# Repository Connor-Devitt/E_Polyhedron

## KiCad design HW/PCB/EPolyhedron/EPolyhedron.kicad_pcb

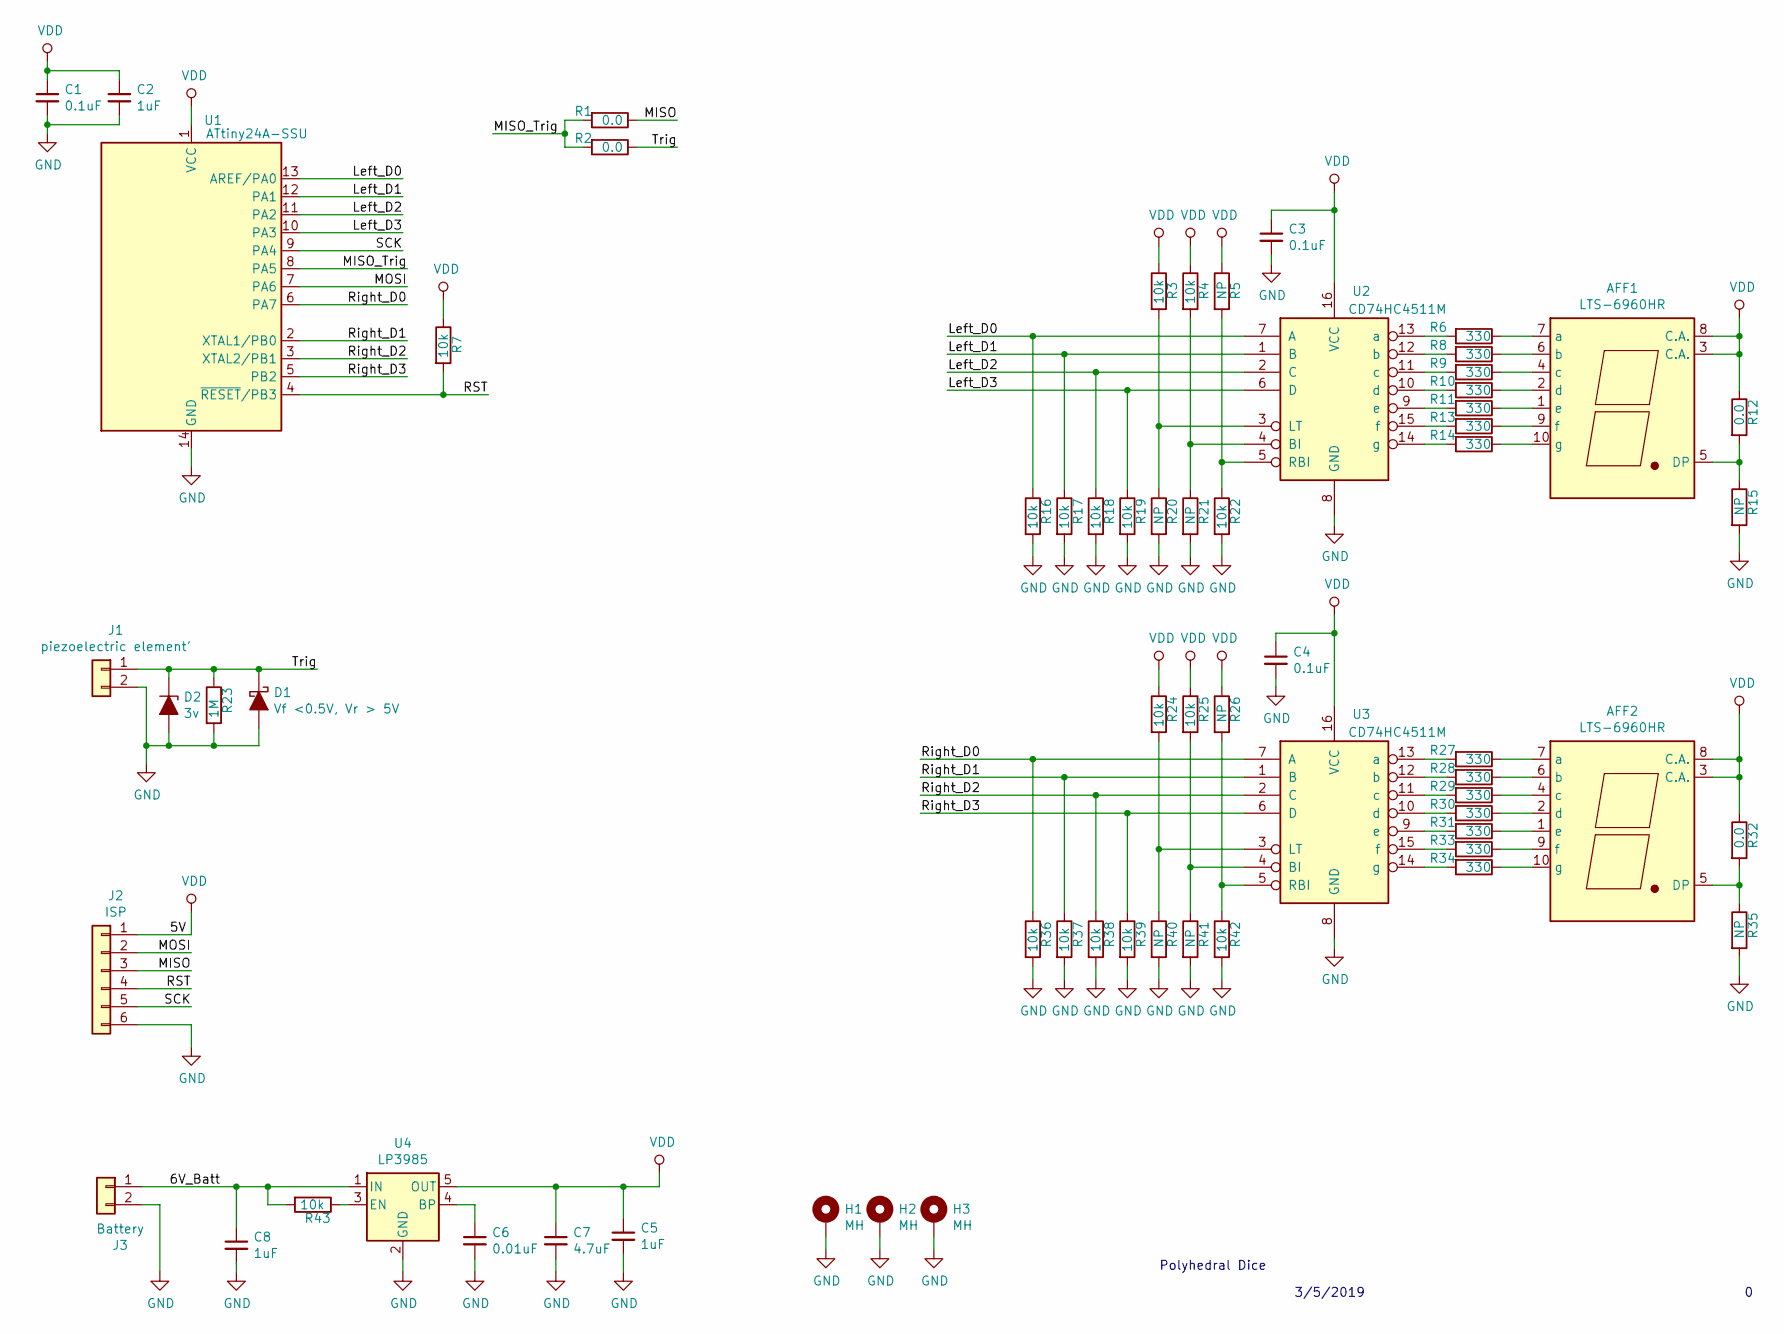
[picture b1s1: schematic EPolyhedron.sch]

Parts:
AFF1, AFF2: LTS-6960HR; 7SegmentLED_LTS6760_LTS6780
C1, C3, C4: 0.1uF; C_0402_1005Metric
C2, C5, C8: 1uF; C_0402_1005Metric
C6: 0.01uF; C_0402_1005Metric
C7: 4.7uF; C_0402_1005Metric
D1: Vf <0.5V, Vr > 5V; D_SOD-323_HandSoldering
D2: 3v; D_SOD-323_HandSoldering
H1, H2, H3: MH; MountingHole_2.2mm_M2_Pad
J1: piezoelectric element'; PinHeader_1x02_P1.27mm_Vertical
J2: ISP; PinHeader_1x06_P1.27mm_Vertical
J3: Battery; BatteryHolder_Keystone_106_1x20mm
R1, R2, R12, R32: 0.0; R_0402_1005Metric
R3, R4, R7, R16, R17, R18, R19, R22, R24, R25, R36, R37, R38, R39, R42, R43: 10k; R_0402_1005Metric
R5, R15, R20, R21, R26, R35, R40, R41: NP; R_0402_1005Metric
R6, R8, R9, R10, R11, R13, R14, R27, R28, R29, R30, R31, R33, R34: 330; R_0402_1005Metric
R23: 1M; R_0402_1005Metric
U1: ATtiny24A-SSU; SOIC-14_3.9x8.7mm_P1.27mm
U2, U3: CD74HC4511M; SOIC-16_3.9x9.9mm_P1.27mm
U4: LP3985; SOT-23-5_HandSoldering

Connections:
/6V_Batt: C8.1, J3.1, R43.2, U4.1 (IN)
/Left_D0: R16.1, U1.13 (AREF/PA0), U2.7 (A)
/Left_D1: R17.1, U1.12 (PA1), U2.1 (B)
/Left_D2: R18.1, U1.11 (PA2), U2.2 (C)
/Left_D3: R19.1, U1.10 (PA3), U2.6 (D)
/MISO: J2.3, R1.1
/MISO_Trig: R1.2, R2.2, U1.8 (PA5)
/MOSI: J2.2, U1.7 (PA6)
/RST: J2.4, R7.2, U1.4 (~RESET~/PB3)
/Right_D0: R36.1, U1.6 (PA7), U3.7 (A)
/Right_D1: R37.1, U1.2 (XTAL1/PB0), U3.1 (B)
/Right_D2: R38.1, U1.3 (XTAL2/PB1), U3.2 (C)
/Right_D3: R39.1, U1.5 (PB2), U3.6 (D)
/SCK: J2.5, U1.9 (PA4)
/Trig: D1.1 (K), D2.1 (K), J1.1, R2.1, R23.1
GND: C1.2, C2.2, C3.2, C4.2, C5.2, C6.2, C7.2, C8.2, D1.2 (A), D2.2 (A), H1.1, H2.1, H3.1, J1.2, J2.6, J3.2, R15.2, R16.2, R17.2, R18.2, R19.2, R20.2, R21.2, R22.2, R23.2, R35.2, R36.2, R37.2, R38.2, R39.2, R40.2, R41.2, R42.2, U1.14 (GND), U2.8 (GND), U3.8 (GND), U4.2 (GND)
unnamed: AFF1.1 (e), R11.1
unnamed: AFF1.2 (d), R10.1
unnamed: AFF1.4 (c), R9.1
unnamed: AFF1.5 (DP), R12.2, R15.1
unnamed: AFF1.6 (b), R8.1
unnamed: AFF1.7 (a), R6.1
unnamed: AFF1.9 (f), R13.1
unnamed: AFF1.10 (g), R14.1
unnamed: AFF2.1 (e), R31.1
unnamed: AFF2.2 (d), R30.1
unnamed: AFF2.4 (c), R29.1
unnamed: AFF2.5 (DP), R32.2, R35.1
unnamed: AFF2.6 (b), R28.1
unnamed: AFF2.7 (a), R27.1
unnamed: AFF2.9 (f), R33.1
unnamed: AFF2.10 (g), R34.1
unnamed: C6.1, U4.4 (BP)
unnamed: R6.2, U2.13 (a)
unnamed: R8.2, U2.12 (b)
unnamed: R9.2, U2.11 (c)
unnamed: R10.2, U2.10 (d)
unnamed: R11.2, U2.9 (e)
unnamed: R13.2, U2.15 (f)
unnamed: R14.2, U2.14 (g)
unnamed: R3.2, R20.1, U2.3 (LT)
unnamed: R4.2, R21.1, U2.4 (BI)
unnamed: R5.2, R22.1, U2.5 (RBI)
unnamed: R24.2, R40.1, U3.3 (LT)
unnamed: R25.2, R41.1, U3.4 (BI)
unnamed: R26.2, R42.1, U3.5 (RBI)
unnamed: R27.2, U3.13 (a)
unnamed: R28.2, U3.12 (b)
unnamed: R29.2, U3.11 (c)
unnamed: R30.2, U3.10 (d)
unnamed: R31.2, U3.9 (e)
unnamed: R33.2, U3.15 (f)
unnamed: R34.2, U3.14 (g)
unnamed: R43.1, U4.3 (EN)
VDD: AFF1.3 (C.A.), AFF1.8 (C.A.), AFF2.3 (C.A.), AFF2.8 (C.A.), C1.1, C2.1, C3.1, C4.1, C5.1, C7.1, J2.1, R3.1, R4.1, R5.1, R7.1, R12.1, R24.1, R25.1, R26.1, R32.1, U1.1 (VCC), U2.16 (VCC), U3.16 (VCC), U4.5 (OUT)

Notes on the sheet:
3/5/2019
Polyhedral Dice

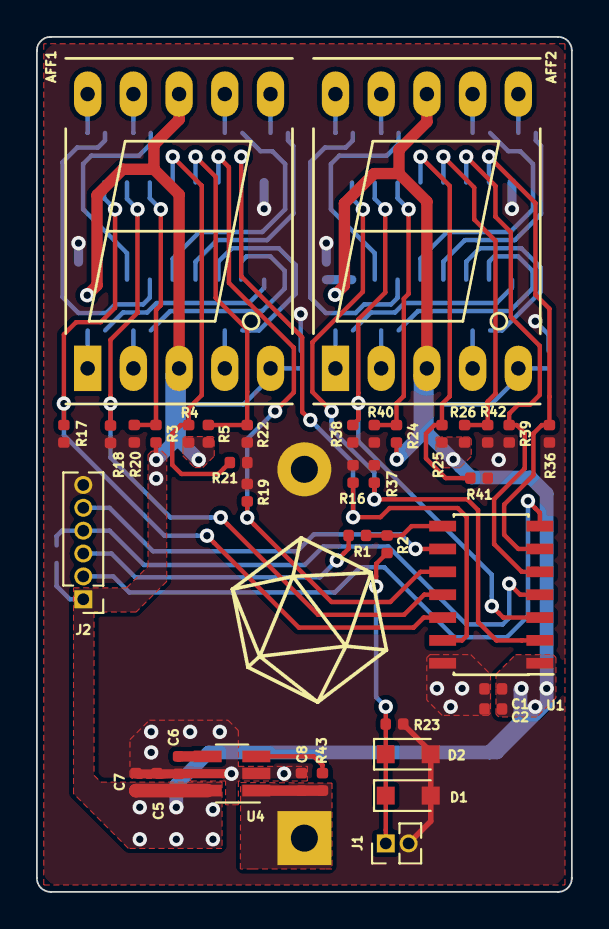
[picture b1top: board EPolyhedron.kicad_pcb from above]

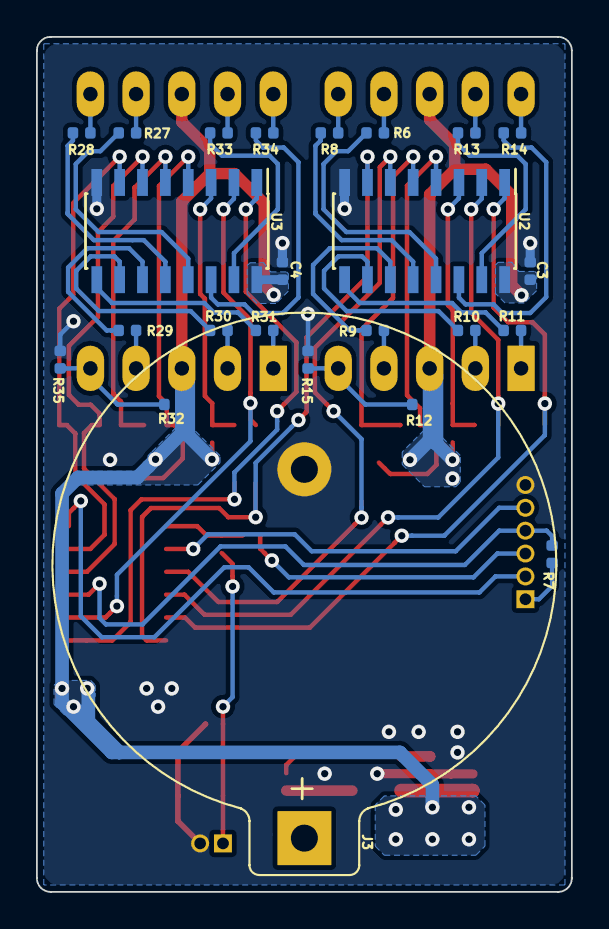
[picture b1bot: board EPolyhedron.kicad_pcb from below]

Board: 2 copper layers, 29.7 x 47.5 mm, 62 parts (24 on the bottom side), 55 nets.

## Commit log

2019-03-31 Added d20 logo to silkscreen
